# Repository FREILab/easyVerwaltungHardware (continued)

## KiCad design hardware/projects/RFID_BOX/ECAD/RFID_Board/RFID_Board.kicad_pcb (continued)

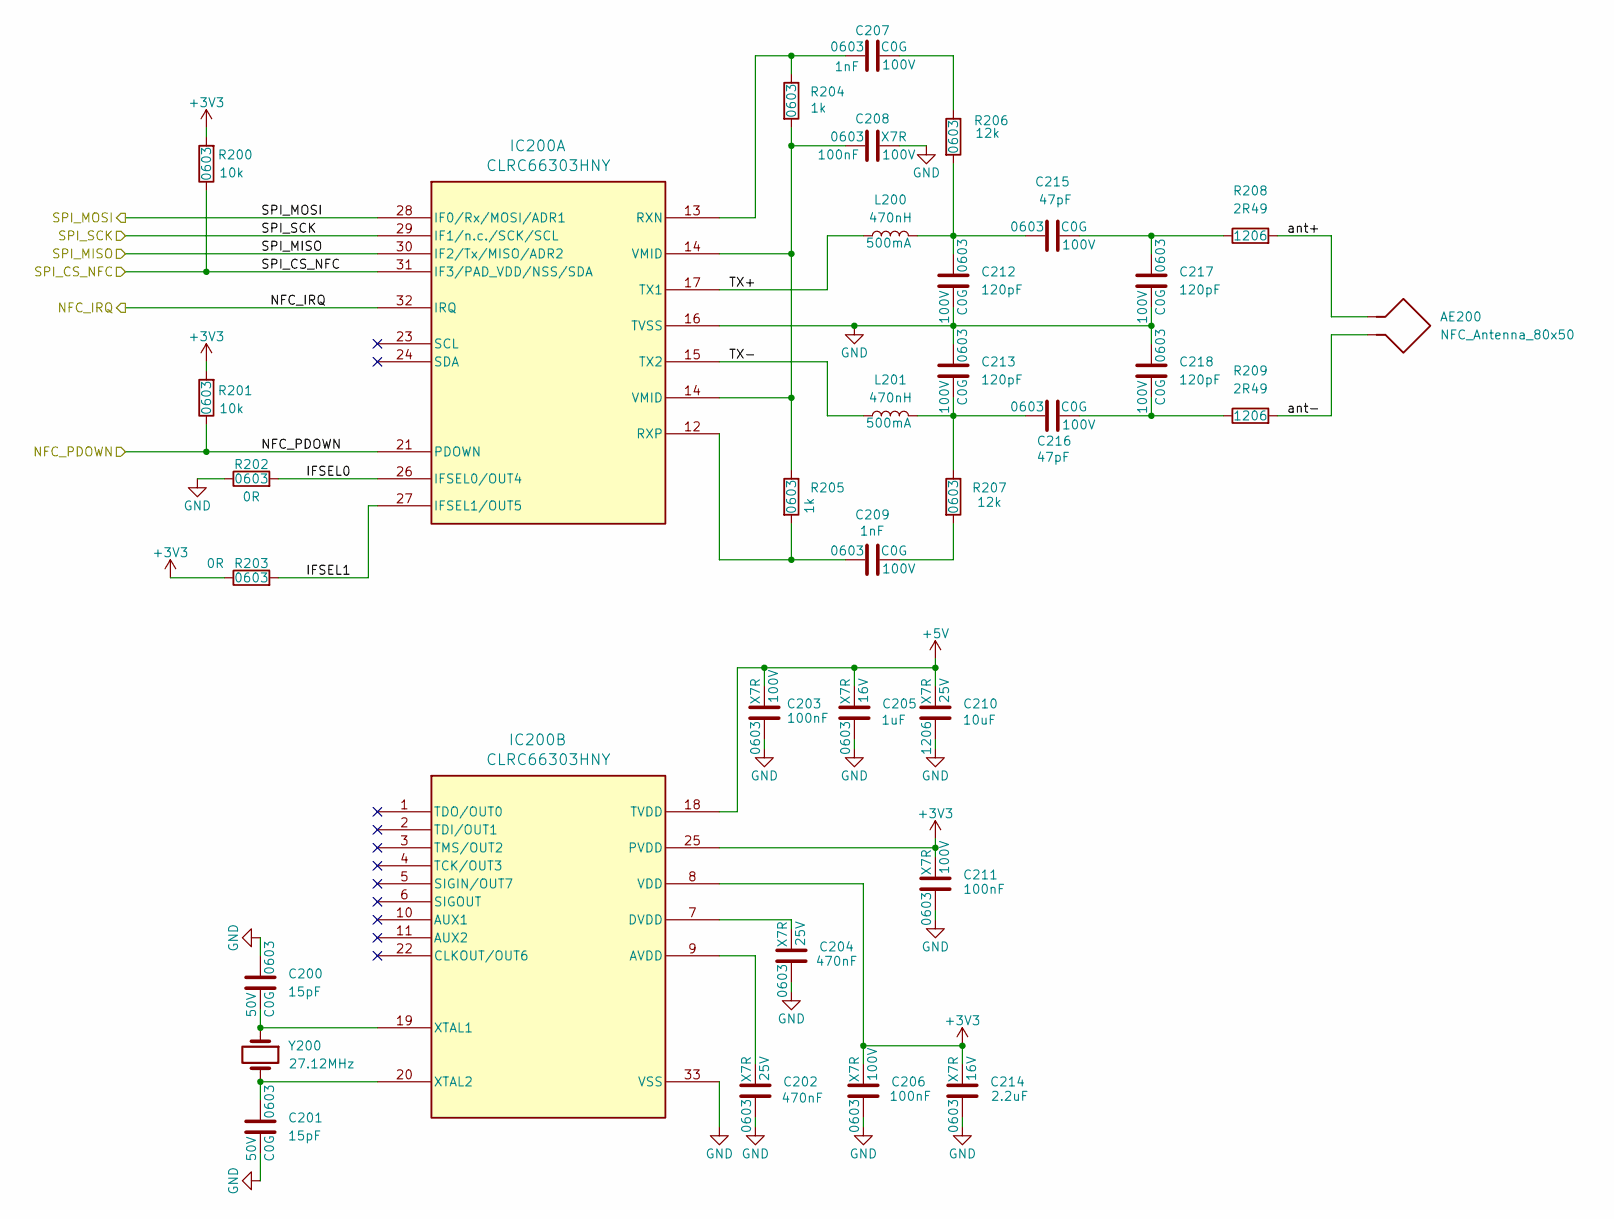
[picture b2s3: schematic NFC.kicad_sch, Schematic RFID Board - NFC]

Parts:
AE200: NFC_Antenna_80x50; NFC_Loop_80x50_5T
C200, C201: 15pF; C_0603_1608Metric; Voltage Rating 50V; Manufacturer Part Number 885012006052
C202, C204: 470nF; C_0603_1608Metric; Voltage Rating 25V; Manufacturer Part Number GRM188R71E474KA12D
C203, C206, C208, C211: 100nF; C_0603_1608Metric; Voltage Rating 100V; Manufacturer Part Number 885012206120
C205: 1uF; C_0603_1608Metric; Voltage Rating 16V; Manufacturer Part Number CGA3E1X7R1C105K080AC
C207, C209: 1nF; C_0603_1608Metric; Voltage Rating 100V; Manufacturer Part Number GCM1885C2A102JA16D
C210: 10uF; C_1206_3216Metric; Voltage Rating 25V; Manufacturer Part Number GRM31CR71E106KA12L
C212, C213, C217, C218: 120pF; C_0603_1608Metric; Voltage Rating 100V; Manufacturer Part Number GCM1885C2A121FA16J
C214: 2.2uF; C_0603_1608Metric; Voltage Rating 16V; Manufacturer Part Number GRM188Z71C225KE43J
C215, C216: 47pF; C_0603_1608Metric; Voltage Rating 100V; Manufacturer Part Number GCM1885C2A470FA16D
IC200: CLRC66303HNY; HVQFN-32-1EP_5x5mm_P0.5mm_EP3.1x3.1mm; Manufacturer Part Number CLRC66303HNY
L200, L201: 470nH; L_0603_1608Metric; Manufacturer Part Number LQW18CNR47J0HD
R200, R201: 10k; R_0603_1608Metric; Tolerance 1%; Manufacturer Part Number CRCW060310K0FKEAC
R202, R203: 0R; R_0603_1608Metric; Tolerance 1%; Manufacturer Part Number CRCW06030000Z0EBC
R204, R205: 1k; R_0603_1608Metric; Tolerance 1%; Manufacturer Part Number CRCW06031K00FKEAC
R206, R207: 12k; R_0603_1608Metric; Tolerance 1%; Manufacturer Part Number CRCW060312K0FKEAC
R208, R209: 2R49; R_1206_3216Metric; Tolerance 1%; Manufacturer Part Number CRCW12062R49FKEA
Y200: 27.12MHz; Y_XRCGB; Manufacturer Part Number XRCGB27M120F3M10R0

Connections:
+3V3: C206.2, C211.2, C214.2, IC200.8 (VDD), IC200.25 (PVDD), R200.2, R201.2, R203.1; also elsewhere on the board
+5V: C203.2, C205.2, C210.2, IC200.18 (TVDD); also elsewhere on the board
/NFC/IFSEL0: IC200.26 (IFSEL0/OUT4), R202.2
/NFC/IFSEL1: IC200.27 (IFSEL1/OUT5), R203.2
/NFC/TX+: IC200.17 (TX1), L200.1
/NFC/TX-: IC200.15 (TX2), L201.1
/NFC/ant+: AE200.1, R208.2
/NFC/ant-: AE200.2, R209.2
/NFC_IRQ: IC200.32 (IRQ); also elsewhere on the board
/NFC_PDOWN: IC200.21 (PDOWN), R201.1; also elsewhere on the board
/SPI_CS_NFC: IC200.31 (IF3/PAD_VDD/NSS/SDA), R200.1; also elsewhere on the board
/SPI_MISO: IC200.30 (IF2/Tx/MISO/ADR2); also elsewhere on the board
/SPI_MOSI: IC200.28 (IF0/Rx/MOSI/ADR1); also elsewhere on the board
/SPI_SCK: IC200.29 (IF1/n.c./SCK/SCL); also elsewhere on the board
GND: C200.1, C201.2, C202.1, C203.1, C204.1, C205.1, C206.1, C208.2, C210.1, C211.1, C212.2, C213.1, C214.1, C217.2, C218.1, IC200.16 (TVSS), IC200.33 (VSS), R202.1; also elsewhere on the board
unnamed: C207.2, R206.1
unnamed: C209.2, R207.2
unnamed: C212.1, C215.1, L200.2, R206.2
unnamed: C213.2, C216.1, L201.2, R207.1
unnamed: C215.2, C217.1, R208.1
unnamed: C216.2, C218.2, R209.1
unnamed: C207.1, IC200.13 (RXN), R204.1
unnamed: C209.1, IC200.12 (RXP), R205.2
unnamed: C208.1, IC200.14 (VMID), R204.2, R205.1
unnamed: C202.2, IC200.9 (AVDD)
unnamed: C204.2, IC200.7 (DVDD)
unnamed: C200.2, IC200.19 (XTAL1), Y200.1
unnamed: C201.1, IC200.20 (XTAL2), Y200.3

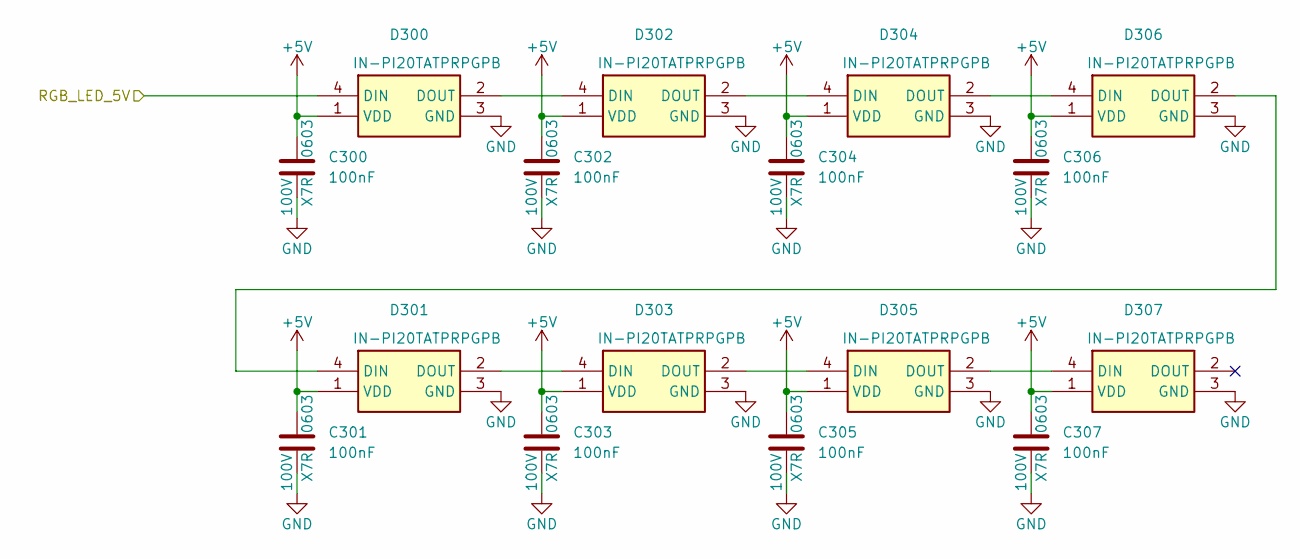
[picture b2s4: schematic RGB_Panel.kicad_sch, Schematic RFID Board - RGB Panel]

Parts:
C300, C301, C302, C303, C304, C305, C306, C307: 100nF; C_0603_1608Metric; Voltage Rating 100V; Manufacturer Part Number 885012206120
D300, D301, D302, D303, D304, D305, D306, D307: IN-PI20TATPRPGPB; LED_INPI20TATPRPGPB; Manufacturer Part Number IN-PI20TATPRPGPB

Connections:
+5V: C300.1, C301.1, C302.1, C303.1, C304.1, C305.1, C306.1, C307.1, D300.1 (VDD), D301.1 (VDD), D302.1 (VDD), D303.1 (VDD), D304.1 (VDD), D305.1 (VDD), D306.1 (VDD), D307.1 (VDD); also elsewhere on the board
/RGB_LED_5V: D300.4 (DIN); also elsewhere on the board
GND: C300.2, C301.2, C302.2, C303.2, C304.2, C305.2, C306.2, C307.2, D300.3 (GND), D301.3 (GND), D302.3 (GND), D303.3 (GND), D304.3 (GND), D305.3 (GND), D306.3 (GND), D307.3 (GND); also elsewhere on the board
unnamed: D300.2 (DOUT), D302.4 (DIN)
unnamed: D301.4 (DIN), D306.2 (DOUT)
unnamed: D301.2 (DOUT), D303.4 (DIN)
unnamed: D302.2 (DOUT), D304.4 (DIN)
unnamed: D303.2 (DOUT), D305.4 (DIN)
unnamed: D304.2 (DOUT), D306.4 (DIN)
unnamed: D305.2 (DOUT), D307.4 (DIN)

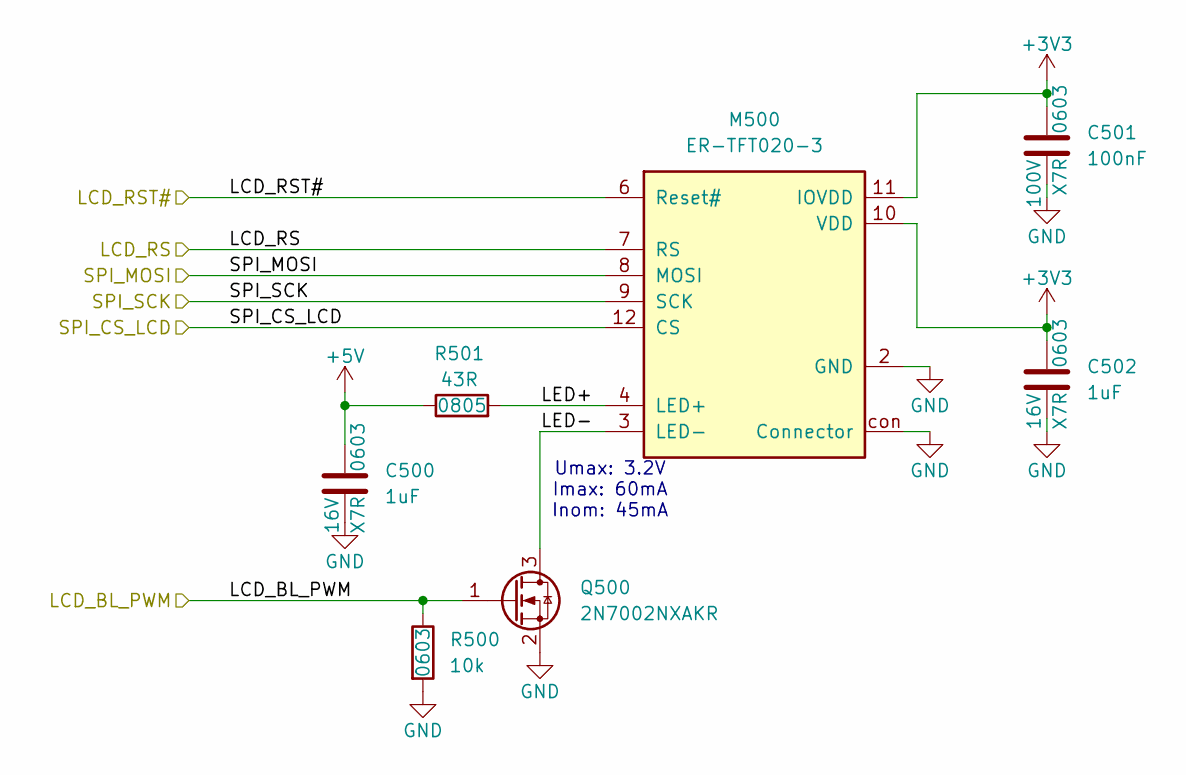
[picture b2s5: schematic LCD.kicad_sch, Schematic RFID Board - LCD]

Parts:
C500, C502: 1uF; C_0603_1608Metric; Voltage Rating 16V; Manufacturer Part Number CGA3E1X7R1C105K080AC
C501: 100nF; C_0603_1608Metric; Voltage Rating 100V; Manufacturer Part Number 885012206120
M500: ER-TFT020-3; LCD_ER-TFT020-3; Manufacturer Part Number FH12-14S-0.5SH(55)
Q500: 2N7002NXAKR; SOT-23; Manufacturer Part Number 2N7002NXAKR
R500: 10k; R_0603_1608Metric; Tolerance 1%; Manufacturer Part Number CRCW060310K0FKEAC
R501: 43R; R_0805_2012Metric; Tolerance 1%; Manufacturer Part Number CRCW080543R0FKEA

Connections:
+3V3: C501.1, C502.1, M500.10 (VDD), M500.11 (IOVDD); also elsewhere on the board
+5V: C500.1, R501.1; also elsewhere on the board
/LCD/LED+: M500.4 (LED+), R501.2
/LCD/LED-: M500.3 (LED-), Q500.3 (D)
/LCD_BL_PWM: Q500.1 (G), R500.1; also elsewhere on the board
/LCD_RS: M500.7 (RS); also elsewhere on the board
/LCD_RST#: M500.6 (Reset#); also elsewhere on the board
/SPI_CS_LCD: M500.12 (CS); also elsewhere on the board
/SPI_MOSI: M500.8 (MOSI); also elsewhere on the board
/SPI_SCK: M500.9 (SCK); also elsewhere on the board
GND: C500.2, C501.2, C502.2, M500.2 (GND), M500.5 (GND), M500.13 (GND), M500.con (Connector), Q500.2 (S), R500.2; also elsewhere on the board

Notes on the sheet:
Umax: 3.2V Imax: 60mA Inom: 45mA

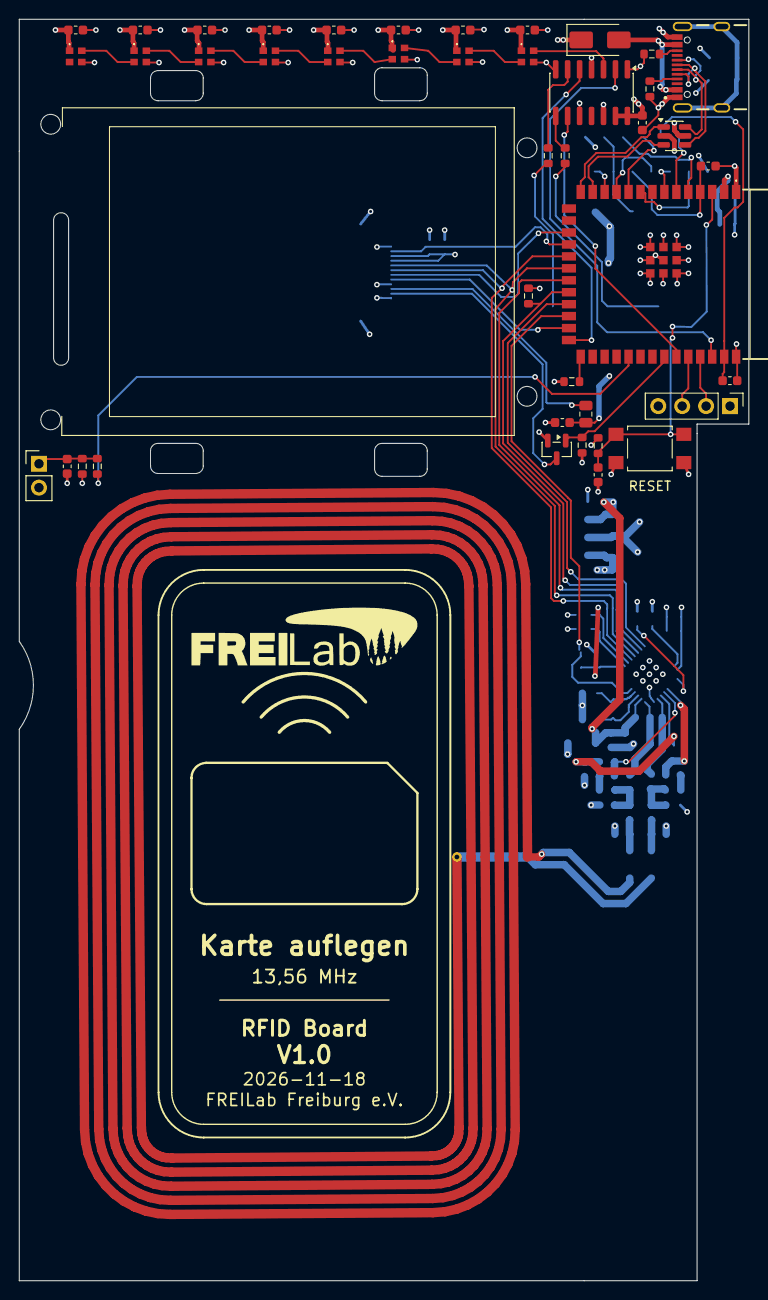
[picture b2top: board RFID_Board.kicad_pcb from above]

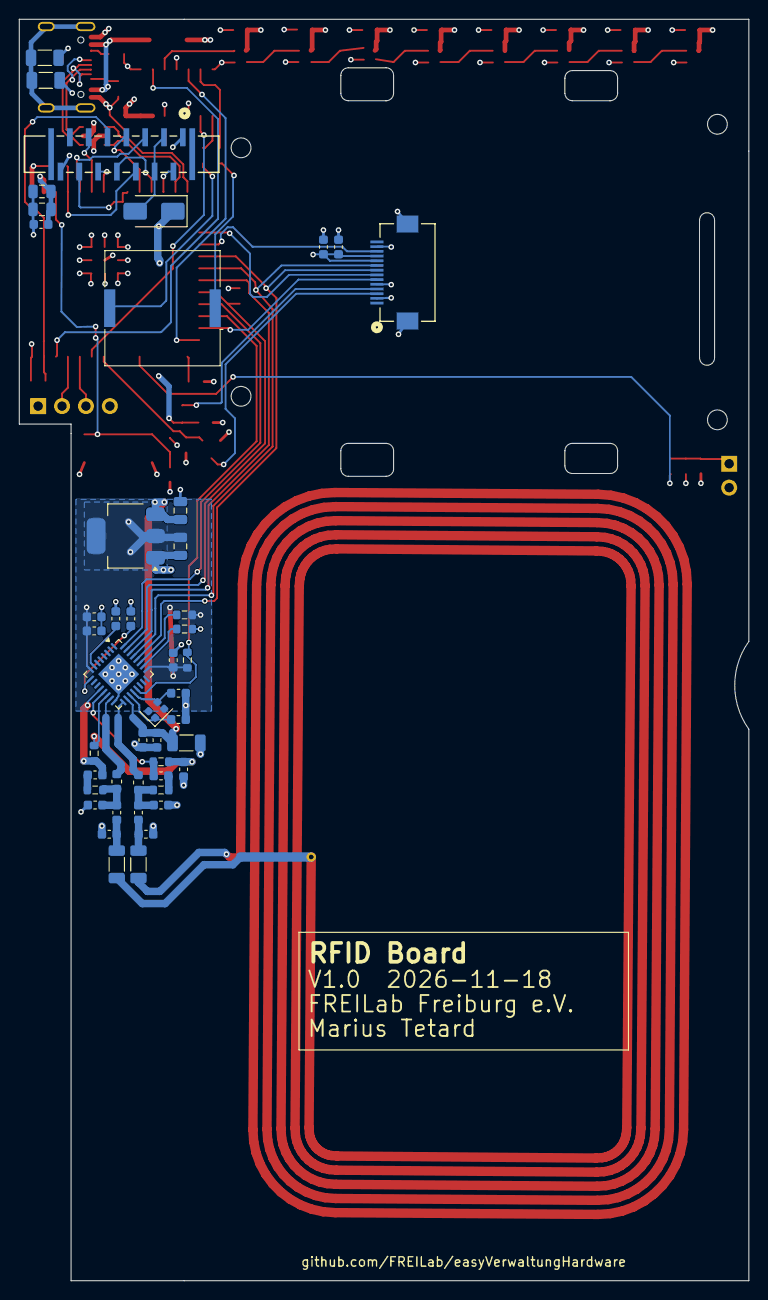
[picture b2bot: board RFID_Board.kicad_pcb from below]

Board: 4 copper layers, 77.5 x 134.0 mm, 90 parts (45 on the bottom side), 73 nets.

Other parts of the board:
LOGO1: Logo_FREILab_24mm

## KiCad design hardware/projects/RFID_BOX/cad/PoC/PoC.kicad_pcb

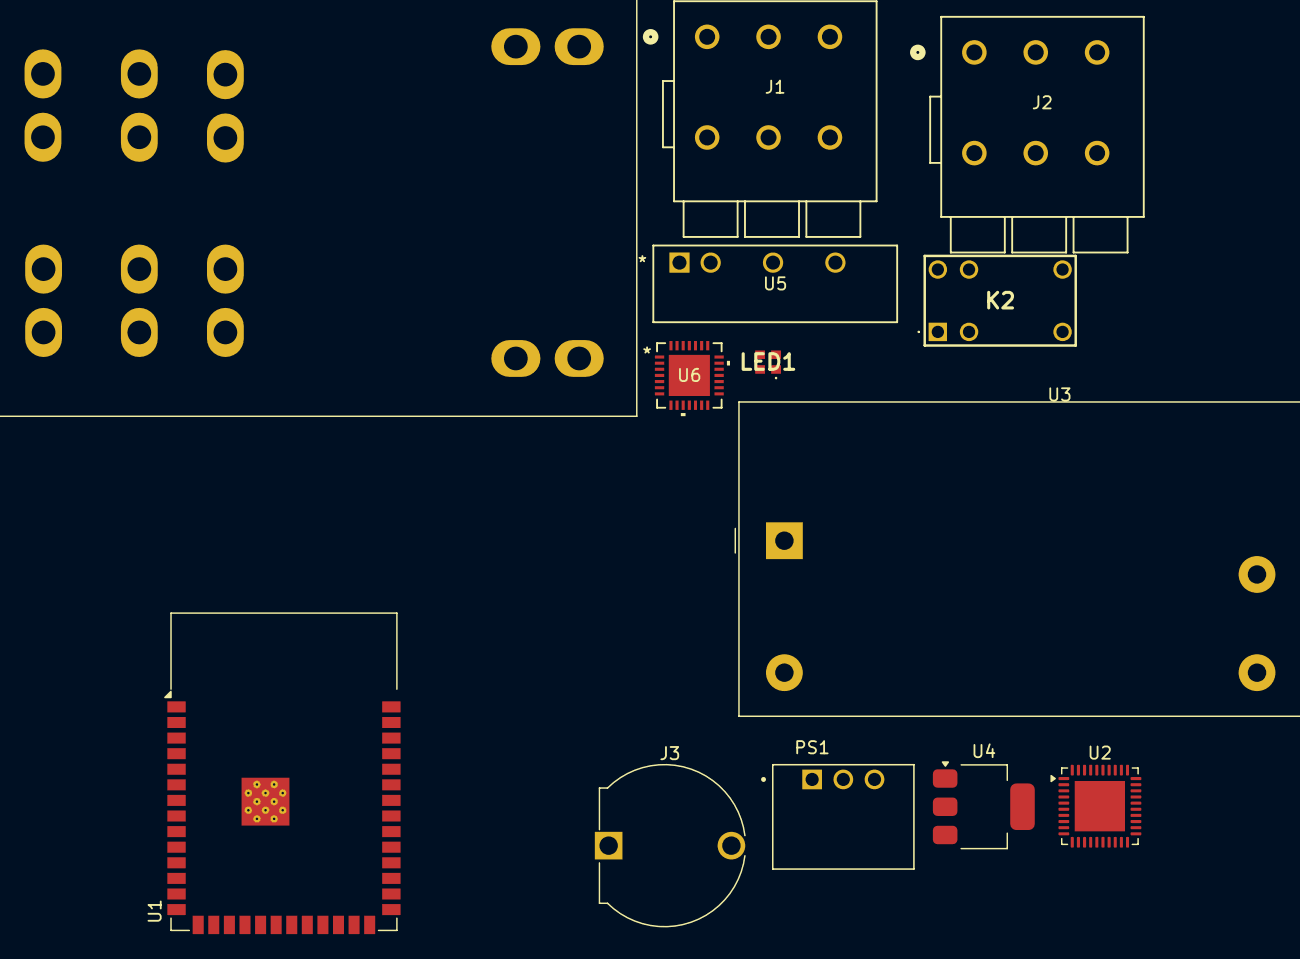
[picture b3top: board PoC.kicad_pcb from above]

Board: 2 copper layers, 13 parts (0 on the bottom side), 9 nets, no tracks yet.

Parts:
J1, J2: J_WAGO_2604-1103; J_2604-1103_WAG
J3: F_696309001002; F_Wurth_WR-FSH_696309001002
K1: T92S11D12-24; K_T92S11D12-24
K2: K_G5V-1-2_DC24
LED1: LED_IN-PI20TATPRPGPB; LED_INPI20TATPRPGPB
PS1: IC_R-78K5.0-2.0; IC_CONV_R-78K5.0-2.0
U1: ESP32-S3-WROOM-1
U2: PN5321A3HN_C1xx; HVQFN-40-1EP_6x6mm_P0.5mm_EP4.1x4.1mm
U3: IC_IRM-10-24; IC_IRM-10-24_THT
U4: AMS1117-3.3; SOT-223-3_TabPin2
U5: IC_RFB-0505S
U6: MCP39F511A-E/MQ; IC_QFN28_MQ_MCH

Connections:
unnamed: J1.1, J1.2
unnamed: J1.3, J1.4
unnamed: J1.5, J1.6
unnamed: J2.1, J2.2
unnamed: J2.3, J2.4
unnamed: J2.5, J2.6
unnamed: K2.5, K2.6
unnamed: U1.1 (GND), U1.40 (GND), U1.41 (GND)
unnamed: U2.11 (AVSS), U2.41 (AVSS)

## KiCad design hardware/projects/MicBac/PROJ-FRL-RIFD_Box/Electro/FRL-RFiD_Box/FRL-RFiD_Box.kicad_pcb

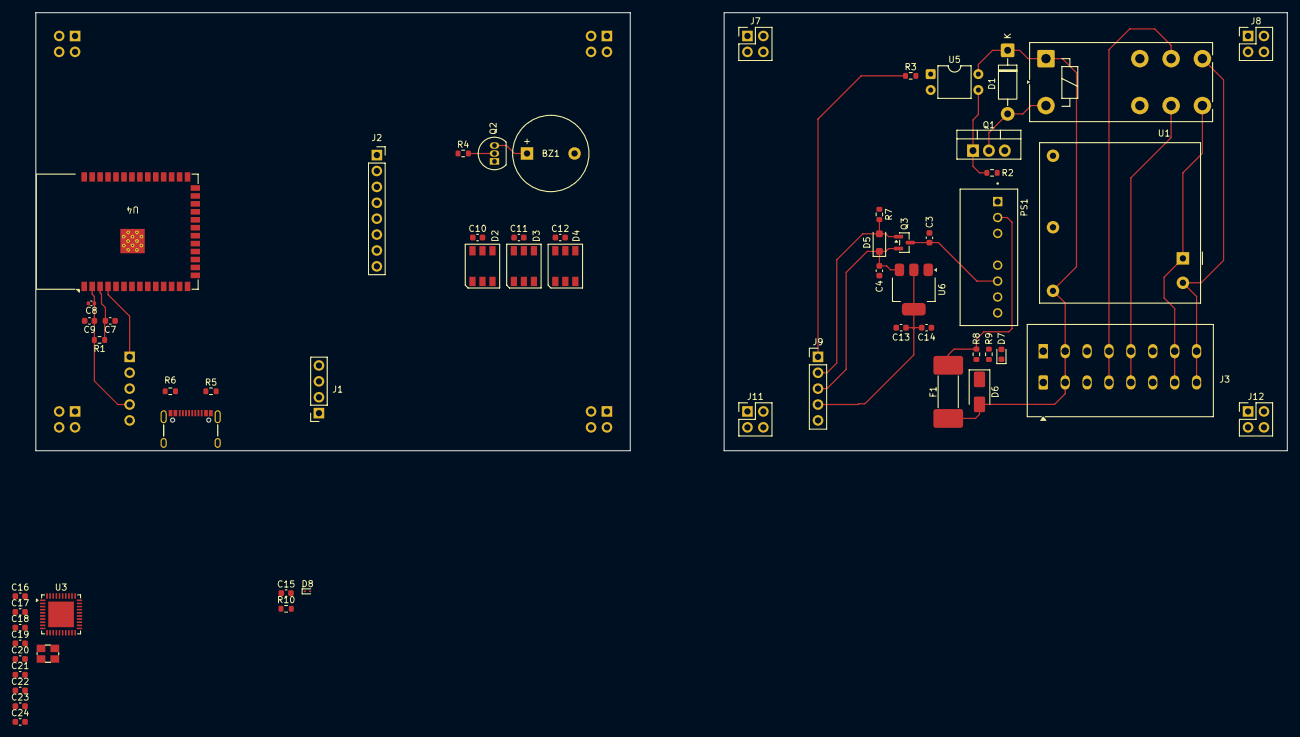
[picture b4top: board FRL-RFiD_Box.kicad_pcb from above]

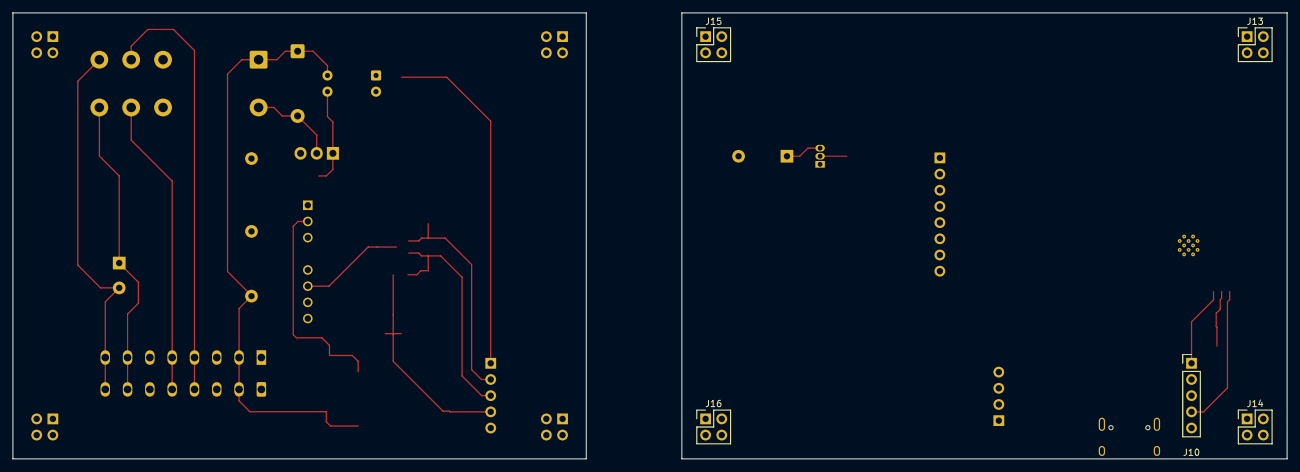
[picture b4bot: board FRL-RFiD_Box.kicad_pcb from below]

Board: 2 copper layers, 200.0 x 70.0 mm, 65 parts (5 on the bottom side), 44 nets.

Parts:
BZ1: TMB12A05; Buzzer_12x9.5RM7.6
C3, C4, C9, C16, C19: 10u; C_0603_1608Metric
C7, C15: 1u; C_0603_1608Metric
C8: 0.1u; C_0402_1005Metric
C10, C11, C12: 0.1uF; C_0603_1608Metric
C13: 22u Tantal or Elko; C_0603_1608Metric
C14, C17, C18, C20, C21: 100n; C_0603_1608Metric
C22: 4,7u; C_0603_1608Metric
C23, C24: 22p; C_0603_1608Metric
D1: 1N4007; D_DO-41_SOD81_P10.16mm_Horizontal
D2, D3, D4: WS2812; LED_WS2812_PLCC6_5.0x5.0mm_P1.6mm
D5: MBR120VLSF; D_SOD-123F
D6: SMAJ36CA; D_SMA
D7: LED G; LED_0603_1608Metric
D8: ESD9B3.3ST5G; D_SOD-923
F1: 200mA T; Fuse_Schurter_UMZ250
J1: I2C_OLED; PinSocket_1x04_P2.54mm_Vertical
J2: SPI_NFC; PinSocket_1x08_P2.54mm_Vertical
J3: WAGO (230V + 24V); TerminalBlock_WAGO_2601-1108_1x08_P3.50mm_Horizontal
J5: USB_C_Receptacle; USB-C_16
J7, J8, J11, J12, J13, J14, J15, J16: Conn_02x02_Odd_Even; PinHeader_2x02_P2.54mm_Vertical
J9, J10: Conn_01x05; PinHeader_1x05_P2.54mm_Vertical
K1: FINDER-41.52.9.024.4311; Relay_DPDT_Finder_40.52
PS1: RS6-2405S; CONV_RS6-2405S
Q1: IRLZ44N; TO-220-3_Vertical
Q2: BC547; TO-92_Inline
Q3: DMG2305UX; SOT-23
R1, R2, R10: 10k; R_0603_1608Metric
R3: 220; R_0603_1608Metric
R4: 1k; R_0603_1608Metric
R5, R6: 5,1k; R_0603_1608Metric
R7: 22k; R_0603_1608Metric
R8, R9: 2k2; R_0603_1608Metric
U1: RAC05-24SK; Converter_ACDC_RECOM_RAC05-xxSK_THT
U3: PN5321A3HN_C1xx; HVQFN-40-1EP_6x6mm_P0.5mm_EP4.1x4.1mm
U4: ESP32-S3-WROOM-1
U5: PC817; DIP-4_W7.62mm
U6: AMS1117-3.3; SOT-223-3_TabPin2
Y1: 27.12MHz; Crystal_SMD_3.2x2.5mm

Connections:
24_GND: D6.1 (A1), D7.1 (K), J3.1, PS1.1 (-VIN), Q1.3 (S), R2.2, U1.4 (-Vout)
+3V3: C8.1, C9.1, J1.4, J2.5, J10.4, R1.2, R10.2, U4.2 (3V3)
+3V3 Bot: C13.1, C14.1, J9.4, U6.2 (VO)
+5V: C10.2, C11.2, C12.2, D2.3 (VCC), D2.5 (VDD), D3.3 (VCC), D3.5 (VDD), D4.3 (VCC), D4.5 (VDD), J10.3, Q2.1 (C)
+5V Bot: C4.1, D5.1 (K), J9.3, Q3.2 (S), U6.3 (VI)
/230V_AC_FINDER_L (OUT): J3.5, K1.21
/230V_AC_FINDER_N (OUT): J3.4, K1.11
/230V_AC_RAC05_L (IN): J3.7, K1.24, U1.1 (AC(L))
/230V_AC_RAC05_N (IN): J3.8, K1.14, U1.2 (AC(N))
/+5V_RS6-2405S_+VOUT: C3.1, PS1.6 (+VOUT), Q3.3 (D)
/+24V_RAC05_OUT: D1.1 (K), D6.2 (A2), F1.1, J3.2, K1.A1, U1.5 (+Vout), U5.4
/+24V_RS6_+VIN: F1.2, PS1.2 (+VIN), R8.1
/BUZZER: R4.1, U4.33 (IO40)
/EN: C7.1, R1.1, U4.3 (EN)
/ESP_IO_0: C15.1, D8.2 (A2), R10.1, U4.27 (IO0)
/I2C_OLED_SCL: J1.1, U4.17 (IO9)
/I2C_OLED_SDA: J1.2, U4.12 (IO8)
/PC817 (OPT): J10.1, U4.4 (IO4)
/PC817 (OPT) Bot: J9.1, R3.1
/SPI_NFC_IRQ: J2.7, U3.25 (P70_IRQ), U4.18 (IO10)
/SPI_NFC_MISO: J2.2, U3.29 (MISO/P71), U4.21 (IO13)
/SPI_NFC_MOSI: J2.3, U3.28 (MOSI/SDA/HSU_TX), U4.20 (IO12)
/SPI_NFC_SCK: J2.1, U3.30 (SCK/P72), U4.22 (IO14)
/SPI_NFC_SS: J2.4, U3.27 (NSS/P50_SCL/HSU_RX), U4.19 (IO11)
/USB_CC1: J5.A5 (CC1), R6.1
/USB_CC2: J5.B5 (CC2), R5.1
/USB_D+: J5.A6 (D+), J5.B6 (D+), U4.14 (USB_D+)
/USB_D-: J5.A7 (D-), J5.B7 (D-), U4.13 (USB_D-)
/VBUS: C16.1, J5.VBUS, J10.2
/VBUS Bot: D5.2 (A), J9.2, Q3.1 (G), R7.1
/WS2812: D2.2 (DIN), U4.5 (IO5)
GND: BZ1.2 (-), C3.2, C4.2, C7.2, C8.2, C9.2, C10.1, C11.1, C12.1, C13.2, C14.2, C15.2, C16.2, C17.2, C18.2, C19.2, C20.2, C21.2, C22.2, C23.2, C24.2, D2.6 (VSS), D3.6 (VSS), D4.6 (VSS), D8.1 (A1), J1.3, J2.6, J5.GND, J5.S (SHIELD), J9.5, J10.5, PS1.7 (-VOUT), R5.2, R6.2, R7.2, U3.1 (DVSS), U3.3 (TVSS1), U3.7 (TVSS2), U3.11 (AVSS), U3.18 (TESTEN), U3.41 (AVSS), U4.1 (GND), U4.40 (GND), U4.41 (GND), U5.2, U6.1 (GND)
unnamed: BZ1.1 (+), Q2.3 (E)
unnamed: D1.2 (A), K1.A2, Q1.2 (D)
unnamed: D2.1 (DOUT), D3.2 (DIN)
unnamed: D3.1 (DOUT), D4.2 (DIN)
unnamed: D7.2 (A), R9.2
unnamed: Q1.1 (G), R2.1, U5.3
unnamed: Q2.2 (B), R4.2
unnamed: R3.2, U5.1
unnamed: R8.2, R9.1
unnamed: C17.1, C18.1, C19.1, C20.1, C21.1, C22.1, U3.5 (TVDD), U3.8 (AVDD), U3.23 (PVDD), U3.39 (DVDD)
unnamed: C23.1, U3.14 (OSCIN), Y1.1
unnamed: C24.1, U3.15 (OSCOUT), Y1.2

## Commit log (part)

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2026-03-01 initial_commit
2026-03-01 move file
2026-03-01 fix typo
2026-03-01 fix intro
2026-03-01 try fix autobuild
2026-03-01 test
2026-03-01 prep tags
2026-03-01 ready for tag
2026-03-01 minor edit
2026-03-01 improve settings and secrets
2026-03-08 clea up comments. code run previosly
2026-03-08 Update Doxyfile project information and input sources
2026-03-08 add to ignore
2026-03-08 Add GitHub Actions workflow for documentation deployment
2026-03-08 add doxy group
2026-03-08 update doxy
2026-04-24 Back to a working state
2026-04-24 tet sucessfull
2026-04-24 update example
2026-04-26 tested, was sucessful, ready to tag
2026-04-30 Baseline OTA implemetation
2026-04-30 Added README and option to set new credentials in secret.h
2026-05-04 Updated Folderstructure and doc
2026-05-05 easyVerwaltung API lib
2026-05-05 minor updates
2026-05-11 Update configuration files and documentation for RFIDBOX project
2026-05-11 Update secret and platformio configuration files for improved clarity and security
2026-05-11 Update backend communication details in secret.h.example for clarity
2026-05-11 Refactor device pairing configurations for clarity and consistency
2026-05-12 Refactor server configuration and enhance logging for authentication processes;
    now working RFID
2026-05-12 Add OTA support with conditional compilation and logging
    all working
2026-05-12 Add workspace configuration for RFIDBOX_PoC project
2026-05-12 started door
2026-05-12 Remove door pair configurations and associated build environments from platformio.ini
2026-05-12 compiliert
2026-05-14 Umbenennung aller Projektordner auf konsistente Namen: - RFIDBOX_PoC → RFID_BOX_legacy - RFIDBOX_Easy → RFID_BOX_easyVerwaltung - RFID_Door_Poc → DOOR_legacy - MachineNodes → MachineNode - RFIDBOX_Po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
    Neuer leerer Projektordner DOOR_easyVerwaltung angelegt (Arduino Uno R4
    WiFi, easyVerwaltung-API, steht noch aus).
    secret.h / secret.h.example vereinheitlicht: WiFi-Credentials nur noch
    in platformio.secrets.ini, nicht doppelt in secret.h. SERVER_HOST statt
    SERVER_IP in allen Projekten.
2026-05-14 Remove unnecessary .gitignore files from door and RFID projects
2026-05-14 remove builds
2026-05-14 auto ignores
2026-05-14 minor changes
2026-05-14 minor fix
2026-05-15 Refactor DOOR project for WiFi support: update platform and board settings, remove Ethernet fallback, and add OTA upload functionality.
2026-05-15 geht im groben
2026-05-15 OTA working
2026-05-15 Add timeout configurations and non-blocking WiFi reconnect logic
2026-05-15 Add watchdog timer support and WiFi reconnect interval configuration
2026-05-15 Refactor UID handling and improve OTA upload response handling
2026-05-15 Refactor deployment configurations and add OTA upload support for multiple environments
2026-05-15 Fix WiFi password definition and update authentication token variable name
2026-05-15 Fix server hostname definition in secret.h.example
2026-05-15 Add 24/7 stability review and improvement recommendations for LASERSAUR_HMI_legacy and RFID_BOX components
2026-05-16 Add Smart Terminal 3D-Print configuration and services setup
2026-05-16 start sceleton
2026-05-17 clean start
2026-05-17 start structure
2026-05-17 compiled
2026-05-17 Refactor project structure: update CMakeLists, add new tasks, and implement blinking functionality
2026-05-17 compiled, läuft
2026-05-17 envs festgelegt, compiled und flashed
2026-05-17 progress
2026-05-17 Update deployment tasks and documentation for USB and OTA methods
2026-05-17 umstieg auf esp32
2026-05-17 Refactor settings and main logic for improved readability and maintainability
2026-05-17 Add server keepalive functionality and update button pin to resolve conflict
2026-05-18 neue pio-env's fuer lasercutterxtool
2026-05-19 Update platformio configurations and add health check functionality for xtool integration
2026-05-19 Add easyAPI library for backend communication
    - Introduced `easyAPI` as a small embedded C library for backend communication in firmware projects.
    - Implemented core functionalities including health checks, login, and heartbeat requests.
    - Added CMake configuration for building the library, tests, and examples.
    - Created example applications demonstrating usage of the API in various modes (single login, heartbeat login, etc.).
    - Included a service layer for non-blocking operations and event handling.
    - Added scripts for running tests and generating coverage reports.
2026-05-19 Add README files for easyVerwaltung projects and legacy counterparts
2026-05-19 start testing
2026-05-19 erstes lebenszeichen vom server
2026-05-19 debuggin rfid
2026-05-19 Update OTA Fleet Plan with current status, open issues, and testing roadmap
2026-05-20 Update .gitignore to include build artifacts for RFID_BOX_easyVerwaltung
2026-05-20 fix prusa xl
2026-05-24 Add Telnet server support and enhance logging in main.cpp
2026-05-24 Add Telnet server functionality and update logging to use TeeStream
2026-05-24 revert
2026-05-24 mehr debug sachen
2026-05-24 usb flash door geht wieder
2026-05-24 Add error JSON files and update WiFi connection logic in main.cpp
2026-05-24 not yet working, mostly network
2026-05-24 Add initial implementation for RFID door control system with OTA support
2026-05-24 Refactor firmware structure for RobotDyn UNO+WiFi R3: - Update README with hardware details and architecture overview. - Enhance platformio.ini for environment configurations. - Implement main logic 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
2026-05-25 Update README and platformio.ini to reflect DHCP IP address usage for OTA
2026-05-25 compiled und flashed
2026-05-25 deploy: e4b3981eeb9ada43625ffa4e166642beba625146
2026-05-25 beret für tests
2026-05-25 geht alles
2026-05-25 sollte jetzt passen, praktischer test
2026-05-25 funktioniert.
2026-05-25 Add ESP8266 WiFi modem functionality and integrate with ATmega
    - Implemented main functionality for ESP8266 to maintain WiFi connection and handle HTTP POST requests from ATmega.
    - Added Telnet debugging support and OTA updates via mDNS.
    - Created settings header for configurable parameters such as WiFi credentials and heartbeat intervals.
    - Introduced new functions for processing serial input, executing HTTP POST requests, and managing WiFi connections.
    - Added error handling for WiFi connection failures and server response codes.
    - Established communication protocol between ESP8266 and ATmega for heartbeat and data transmission.
2026-05-25 Update README files for various projects: add flashing and debugging instructions, clarify hardware details, and outline project status and API communication.
2026-05-25 Update README.md: Revise hardware overview and system architecture sections for clarity and completeness
2026-05-25 deploy: 56db210fe6f375ec91b751eadf4b23cb9ffa2d83
2026-05-25 Update README.md: Add details about onboard and external current sensor variants for machine hour tracking
2026-05-25 Update platformio.ini: Add missing line for build flags configuration
2026-05-27 wokwi diagram & config
2026-05-29 poc loki & improved wokwi
2026-06-05 Enhance network reliability: Implement WiFi stack reset after consecutive connection failures and ensure network services restart on reconnect
2026-06-15 Add debug logging and server health check functionality for improved diagnostics
2026-06-16 Increase buffer sizes in busDbg function for enhanced logging capabilities
2026-06-16 Refactor waitMotorOK function to accept LED state parameters and implement RFID debounce cooldown to prevent duplicate events
    -> läuft stabil und schnell
2026-06-17 Add debug message handling for ATMDBG in ESP module and enhance logging in ATmega
2026-06-17 Implement periodic health checks for RFID module and reinitialize if unresponsive
2026-06-27 add old files
